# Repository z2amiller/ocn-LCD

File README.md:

# ocn-LCD

A coin-cell elapsed-time counter with a 4-digit LCD and a magnetic off switch. While a magnet
sits at the marked end, the board is switched off. Take the magnet away and it powers up and counts
elapsed time in hours and minutes, up to 99:59 (about 100 hours). Put the magnet back and it powers
down a few seconds later; the next time the magnet comes off, counting starts again from 00:00.

The renders leave out the LCD (on the back), the coin-cell holder and the reed switch, which have no
3D models.

Status: revision 0.1, not yet built. The firmware is in [firmware/](firmware/): it runs on TI's
MSP430FR4133 LaunchPad, and its driver for this board's LCD hasn't been tried on real glass yet.

## How it works

- **Counting.** An MSP430FR4131 drives the LCD directly with its built-in LCD controller and keeps
  time from a 32.768 kHz crystal. It spends almost all its time in its deepest sleep mode with the
  display still running, so it should draw 1–2 µA while counting (see the power budget below).
- **Magnet switch.** The magnet closes a normally open reed switch (SW1). That pulls the gate of a
  P-channel MOSFET (Q1) up to the cell voltage and cuts power to everything after it. With the
  magnet away, a 10 MΩ resistor pulls the gate low and the board runs. While switched off, the only
  drain on the cell is that resistor, about 0.3 µA.
- **Reset on purpose, not by accident.** 14 µF of capacitance after the switch keeps the board
  running for several seconds after the magnet arrives, so a brief knock or switch bounce does not
  reset the count. Leaving the magnet in place longer than that powers the board down and clears it.
- **Display.** The LCD is a Good Display GDC04212: 4 digits with a colon, 1/4 duty, 3 V. It mounts
  on the back of the board, so the front carries every surface-mount part.

## Power budget

Estimates at 3.0 V and 25 °C, from the TI datasheet (SLAS865) and the part specs. They will be
replaced by measurements on the board. Until then, the firmware's
[measurements on the LaunchPad](firmware/README.md#measured-on-the-launchpad) are the nearest guide:
2.2 µA asleep with its much larger LCD.

| Item | Counting (magnet away) | Off (magnet in place) | Basis |
|---|---|---|---|
| MCU asleep (LPM3.5), with the 32 kHz crystal, RTC, LCD controller and charge pump running | 0.94 µA | 0 | Datasheet typical, supervisor (SVS) off |
| LCD glass: recharging the segments about 30 times a second | 0.2–1 µA | 0 | Estimate from typical TN glass capacitance (~2 nF); the biggest unknown |
| Waking once a minute to advance the count and rewrite the display | ~0.01 µA | 0 | ~2 ms at ~0.4 mA per wake; waking every second instead would cost ~0.8 µA |
| Colon blink | ~0 | 0 | Done by the LCD hardware, no CPU wake |
| Gate pull-down R3 (10 MΩ across the cell while the reed is closed) | 0 | 0.3 µA | 3.0 V / 10 MΩ |
| Q1 MOSFET leakage while off | – | a few nA | Typical; the datasheet maximum is specified at 30 V |
| Hold-up capacitors C1–C3, leakage | ~1 nA | 0 | MLCC insulation resistance; under 0.1 µA even at the spec minimum |
| Reset pull-up, reed switch, unused pins (driven low) | 0 | 0 | No DC path |
| **Total** | **about 1.2–2 µA** | **about 0.3 µA** | |

Estimated runtime on one CR2032 (225 mAh nominal), allowing about 1 %/year for the cell's own
self-discharge:

| Mode | Estimated runtime |
|---|---|
| Counting continuously | about 11–18 years |
| Off (magnet in place) | over 40 years |

Both are longer than a CR2032's rated shelf life of about 10 years, so in practice the cell's age
sets the limit, not this circuit. Cold reduces the cell's usable capacity, so expect less in cold
conditions.

Firmware choices that keep it there:
- Leave the voltage supervisor (SVS) off in LPM3.5; it costs about 0.2 µA. The brownout reset stays
  on regardless.
- Update the count once a minute, not once a second.
- Blink the colon with the LCD hardware, not by waking the CPU.
- Drive every unused pin low, including the RX pin when nothing is connected to it.

## Placing the magnet

The reed switch is at the end marked MAGNET DISABLE and runs along the length of the board. It
responds to field along its own length, so use a magnet magnetized through its flat faces (a
neodymium cylinder or disc), at that end, with its axis along the board and its face toward the
board's end. SW1's axis is 4.4 mm in from the long edge that carries the LCD pins, and a magnet
centered on that line gives the most margin.

A magnet centered on the board's width sits about 9 mm off SW1's axis and puts roughly half to a
quarter as much field along it. Even so, a model of a typical 10 × 8 mm N42 cylinder (no nearby
steel) gives several times the switch's ~2–3 mT pull-in out to about 20 mm. Check the actual magnet
on the bench, especially if steel sits near it.

The switch lets go only once the magnet is a few centimeters away (the same model puts it at about
35–40 mm in line), so move the magnet well clear to start counting.

## Key parts

| Ref | Part | LCSC |
|---|---|---|
| U1 | TI MSP430FR4131IPM, LQFP-64 (FR4132/FR4133 also fit) | C1879660 |
| DS1 | Good Display GDC04212 4-digit LCD, 12 pins at 2.54 mm | none (hand-soldered) |
| BT1 | Lian Xin BS-CR2032-8 coin-cell holder, for a CR2032 | C7498149 |
| SW1 | Littelfuse 59170-1-S-00-D reed switch, normally open, 10–15 AT | C315909 |
| Q1 | AO3401A P-channel MOSFET, SOT-23 | C15127 |
| Y1 | TKD SF32WK32768D31T002 32.768 kHz crystal, 3215, 12.5 pF (any 3215 12.5 pF crystal fits) | C271654 |

Every part in the BOM carries its LCSC number. The LCD, J1 and TP3 are left out of the BOM and the
placement file. The passives are 0603 and 1206.

## Ordering

JLCPCB can make the board and fit all the surface-mount parts. [docs/ORDERING.md](docs/ORDERING.md)
walks through the order, screen by screen.

## Assembly

1. **Surface-mount parts first, all on the front.** A stencil helps with the 0.5 mm pitch MCU. The
   holder and the reed switch are rated for reflow, so a hotplate works.
2. **LCD last, by hand.** The LCD is through-hole on the back. Solder it after reflow and keep the
   iron off the glass. The silkscreen marks its pin 1.
3. **Programming header (J1).** It is only needed on the bench.
4. **Battery.** Fit the CR2032 after programming.

## Programming

The MCU is programmed over Spy-Bi-Wire from the eZ-FET programmer on a TI MSP-EXP430FR4133
LaunchPad. Any MSP430 LaunchPad with an eZ-FET should also work. J1 carries the four programming
signals plus the MCU's serial port.

1. **Take the coin cell out.** The LaunchPad powers the board at 3.3 V, and with a cell fitted it
   would push current back into it. The board's silkscreen says so too.
2. **Pull every jumper off the LaunchPad's J101 isolation block.** That disconnects the
   LaunchPad's own MCU, so the eZ-FET talks only to this board.
3. **Wire J1 to J101 with dupont jumpers.** Use the J101 pins on the eZ-FET (emulator) side, not the
   side that runs to the LaunchPad's own MCU:

   | ocn-LCD J1 | LaunchPad J101, eZ-FET side |
   |---|---|
   | 3V | 3V3 |
   | R | SBW RST |
   | T | SBW TST |
   | GND | GND |
   | RX (optional, serial) | RXD |
   | TX (optional, serial) | TXD |

   The serial names match straight across. J101 labels its pins from the target MCU's point of
   view, so its RXD carries data into this board's RX.

4. **Flash the firmware** with TI UniFlash or Code Composer Studio. Select the MSP430FR4131 and the
   LaunchPad's eZ-FET as the connection. Or, with msp430-gcc and DSLite installed (see
   [firmware/README.md](firmware/README.md)), run `make GLASS=gdc04212 MCU=msp430fr4131 flash` in
   `firmware/`.
5. **Unplug the LaunchPad before measuring current or fitting the cell.** The programming and
   serial lines draw current of their own.

**Measuring battery current.** R2 (1 Ω, 1206) sits in series with the cell. Lift it and connect a
current meter across its pads. TP3 is a test pad on the switched 3 V supply.

## Files

- `ocn-LCD.kicad_pro`, `.kicad_sch` and `.kicad_pcb`: the KiCad 10 project. The board is 27 × 65.4 mm,
  two layers.
- `lib/`: the board's own symbols and footprints: the MSP430FR413x, the GDC04212 and its footprint,
  the coin-cell holder and the reed switch. The project's library tables point at this folder, so the
  project opens without any other library installed.
- `firmware/`: the MCU's firmware, in C for msp430-gcc, with its own README covering how it works, how
  to build and flash it, and the current measurements.
- `GERBER-ocn-LCD.zip` and `jlcpcb/production_files/` (BOM and CPL): the JLCPCB fabrication and
  assembly files. [docs/ORDERING.md](docs/ORDERING.md) explains how to use them.

## License

The board (everything outside `firmware/`) is licensed under the **CERN Open Hardware Licence
Version 2 – Permissive** (CERN-OHL-P v2). See [LICENSE](LICENSE) and [NOTICE](NOTICE).

You may make, modify, and sell boards from these files, with no obligation to
publish your changes.

The firmware in `firmware/` is licensed under the **MIT License**; see
[firmware/LICENSE](firmware/LICENSE). It is just as permissive, in the form usual for software.

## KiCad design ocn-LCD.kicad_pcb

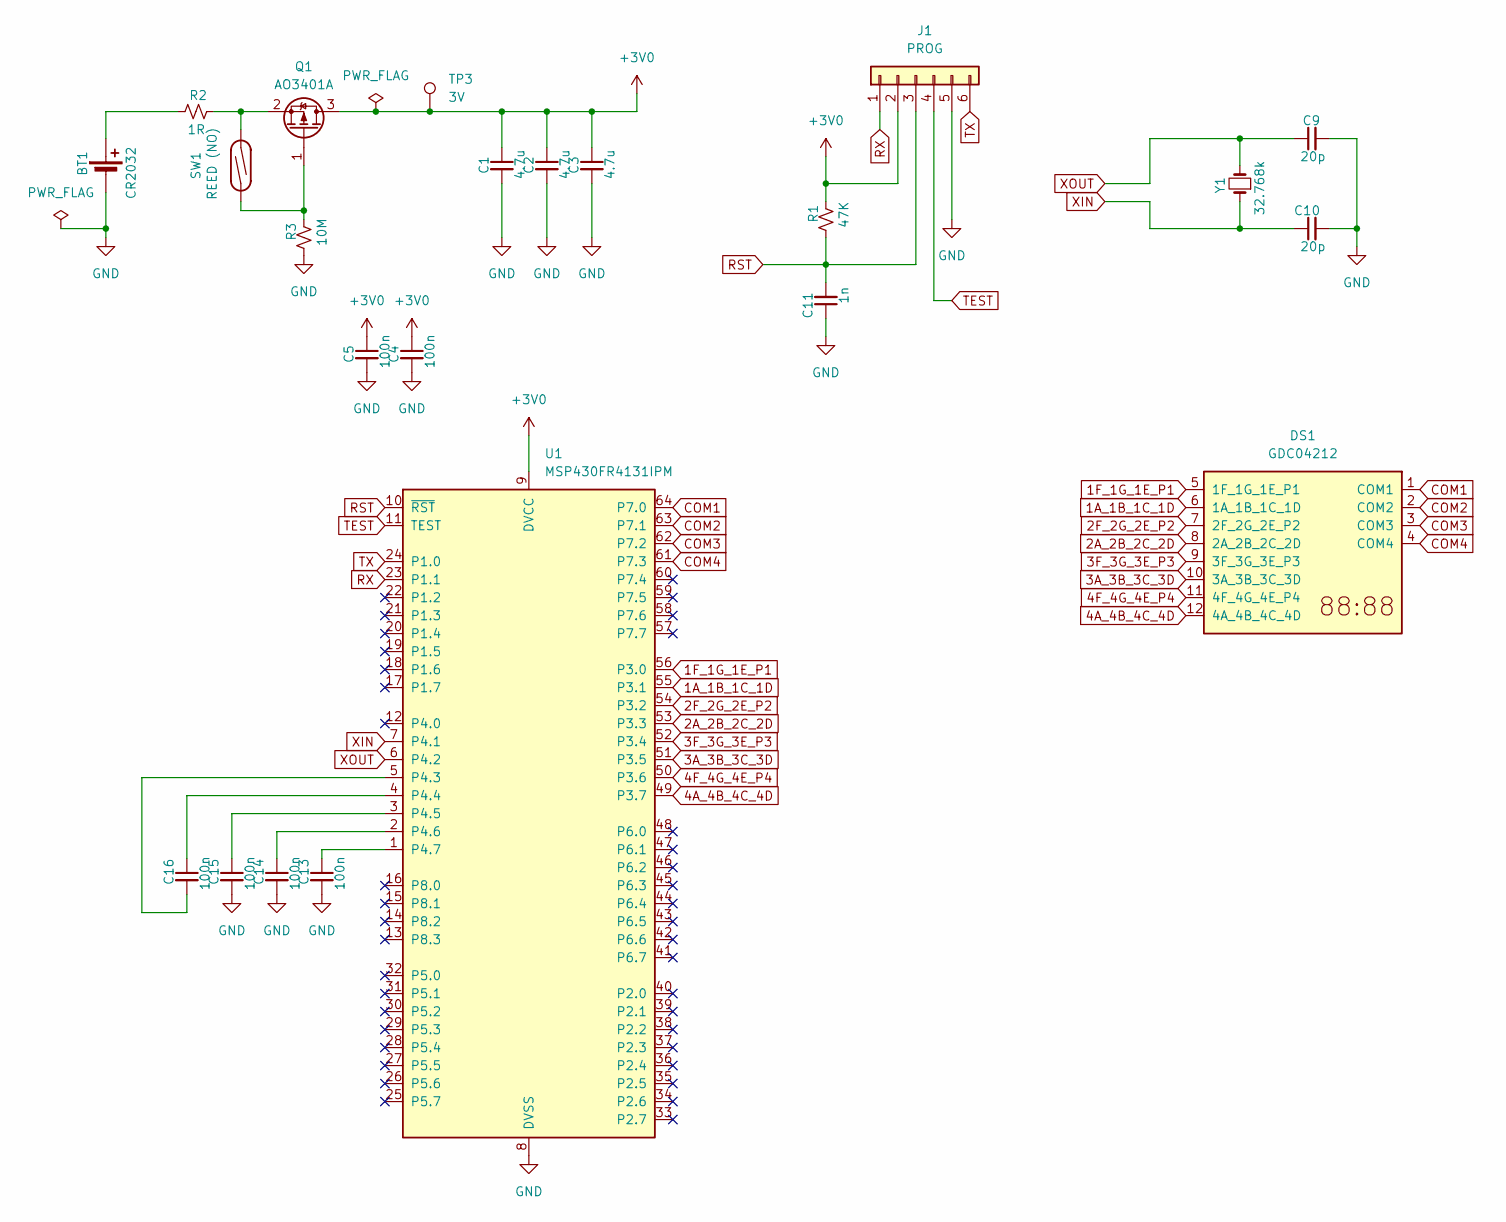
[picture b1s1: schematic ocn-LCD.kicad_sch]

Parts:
BT1: CR2032; BatteryHolder_LianXin_BS-CR2032-8_1x2032; LCSC C7498149
C1, C2, C3: 4.7u; C_1206_3216Metric; LCSC C29823
C4, C5, C13, C14, C15, C16: 100n; C_0603_1608Metric; LCSC C14663
C9, C10: 20p; C_0603_1608Metric; LCSC C1648
C11: 1n; C_0603_1608Metric; LCSC C1588
DS1: GDC04212; LCD_GDC04212_1x12_P2.54mm
J1: PROG; PinHeader_1x06_P2.54mm_Vertical
Q1: AO3401A; SOT-23; LCSC C15127
R1: 47K; R_0603_1608Metric; LCSC C25819
R2: 1R; R_1206_3216Metric; LCSC C17928
R3: 10M; R_0603_1608Metric; LCSC C7250
SW1: REED (NO); SW_SPST_REED_Littelfuse_59170_GullWing; LCSC C315909
TP3: 3V; TestPoint_Pad_1.5x1.5mm
U1: MSP430FR4131IPM; LQFP-64_10x10mm_P0.5mm; LCSC C1879660
Y1: 32.768k; Crystal_SMD_3215-2Pin_3.2x1.5mm; LCSC C271654

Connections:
1A_1B_1C_1D: DS1.6 (1A_1B_1C_1D), U1.55 (P3.1)
1F_1G_1E_P1: DS1.5 (1F_1G_1E_P1), U1.56 (P3.0)
2A_2B_2C_2D: DS1.8 (2A_2B_2C_2D), U1.53 (P3.3)
2F_2G_2E_P2: DS1.7 (2F_2G_2E_P2), U1.54 (P3.2)
3A_3B_3C_3D: DS1.10 (3A_3B_3C_3D), U1.51 (P3.5)
3F_3G_3E_P3: DS1.9 (3F_3G_3E_P3), U1.52 (P3.4)
4A_4B_4C_4D: DS1.12 (4A_4B_4C_4D), U1.49 (P3.7)
4F_4G_4E_P4: DS1.11 (4F_4G_4E_P4), U1.50 (P3.6)
+3V0: C1.1, C2.1, C3.1, C4.1, C5.1, J1.2, Q1.3 (D), R1.1, TP3.1 (1_1), U1.9 (DVCC)
COM1: DS1.1 (COM1), U1.64 (P7.0)
COM2: DS1.2 (COM2), U1.63 (P7.1)
COM3: DS1.3 (COM3), U1.62 (P7.2)
COM4: DS1.4 (COM4), U1.61 (P7.3)
GND: BT1.2 (-), C1.2, C2.2, C3.2, C4.2, C5.2, C9.2, C10.2, C11.1, C13.2, C14.2, C15.2, J1.5, R3.2, U1.8 (DVSS)
unnamed: BT1.1 (+), R2.2
unnamed: Q1.1 (G), R3.1, SW1.1
unnamed: Q1.2 (S), R2.1, SW1.2
unnamed: C16.2, U1.5 (P4.3)
unnamed: C16.1, U1.4 (P4.4)
unnamed: C15.1, U1.3 (P4.5)
unnamed: C14.1, U1.2 (P4.6)
unnamed: C13.1, U1.1 (P4.7)
RST: C11.2, J1.3, R1.2, U1.10 (~RST)
RX: J1.1, U1.23 (P1.1)
TEST: J1.4, U1.11 (TEST)
TX: J1.6, U1.24 (P1.0)
XIN: C10.1, U1.7 (P4.1), Y1.1
XOUT: C9.1, U1.6 (P4.2), Y1.2

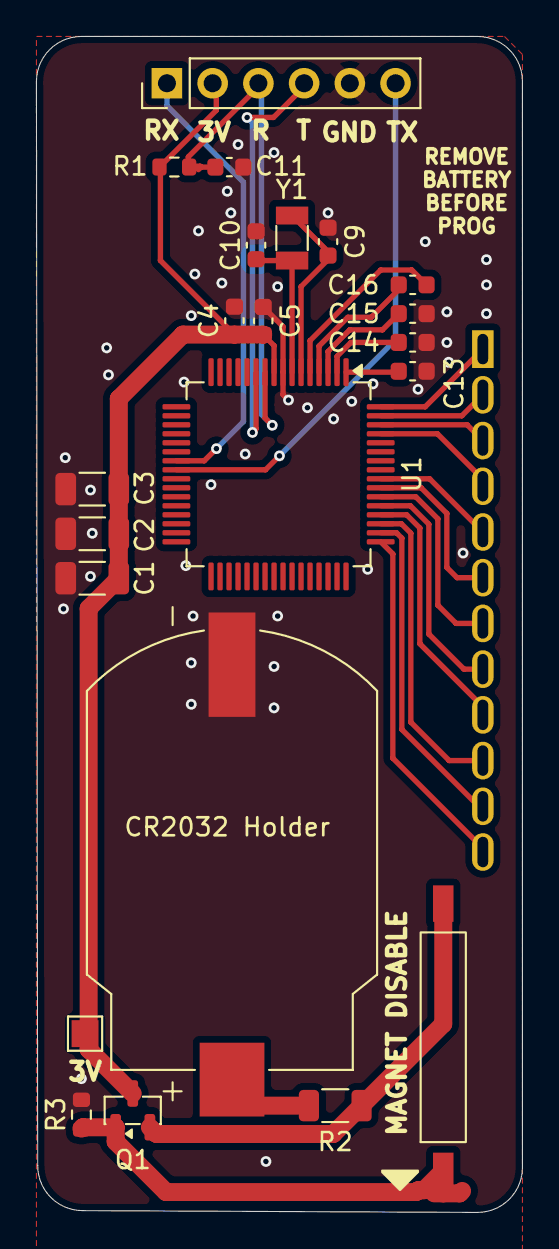
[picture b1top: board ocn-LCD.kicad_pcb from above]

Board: 2 copper layers, 27.0 x 65.3 mm, 23 parts (1 on the bottom side), 28 nets.

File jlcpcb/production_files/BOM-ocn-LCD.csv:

Comment,Designator,Footprint,LCSC,Quantity
100n,"C13,C14,C15,C16,C4,C5",C_0603_1608Metric,C14663,6
10M,R3,R_0603_1608Metric,C7250,1
1R,R2,R_1206_3216Metric,C17928,1
1n,C11,C_0603_1608Metric,C1588,1
20p,"C10,C9",C_0603_1608Metric,C1648,2
32.768k,Y1,Crystal_SMD_3215-2Pin_3.2x1.5mm,C271654,1
4.7u,"C1,C2,C3",C_1206_3216Metric,C29823,3
47K,R1,R_0603_1608Metric,C25819,1
AO3401A,Q1,SOT-23,C15127,1
CR2032,BT1,BatteryHolder_LianXin_BS-CR2032-8_1x2032,C7498149,1
GDC04212,DS1,LCD_GDC04212_1x12_P2.54mm,C9900333183,1
MSP430FR4131IPM,U1,LQFP-64_10x10mm_P0.5mm,C1879660,1
REED (NO),SW1,SW_SPST_REED_Littelfuse_59170_GullWing,C315909,1

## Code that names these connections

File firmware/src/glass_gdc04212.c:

// SPDX-License-Identifier: MIT
// The board's glass: Good Display GDC04212, 4 digits with a colon, 1/4 duty, 1/3 bias, 3.0 V. Derived from the
// spec sheet's pin table (as encoded in the GDC04212 symbol in ../lib/LowPower.kicad_sym) and the board's
// netlist; not yet checked on real glass.
//
// Glass pins 1-4 are COM1-COM4, wired to P7.0-P7.3 = L0-L3 (MCU COM0-COM3), as on the LaunchPad. The segment
// pins are wired in order to P3.0-P3.7 = L8-L15:
//
//   glass pin   MCU pin   segment on COM1  COM2  COM3  COM4
//       5        L8              1F        1G    1E    P1
//       6        L9              1A        1B    1C    1D
//       7        L10             2F        2G    2E    P2 (colon)
//       8        L11             2A        2B    2C    2D
//       9        L12             3F        3G    3E    P3
//      10        L13             3A        3B    3C    3D
//      11        L14             4F        4G    4E    P4
//      12        L15             4A        4B    4C    4D
//
// Each LCDMEM byte covers two pins: the even pin's COM3..COM0 in bits 3..0, the odd pin's in bits 7..4. So digit n
// is LCDMEM[3 + n], and every digit's byte has the same layout. P1, P3 and P4 are decimal points.
#include <msp430.h>
#include "glass.h"

// TI's header declares LCDMEM and LCDBMEM as pointers to a one-byte register, so indexing past 0 trips
// -Warray-bounds even though the memory is there.
#pragma GCC diagnostic ignored "-Warray-bounds"

#define SEG_F 0x01                               // even pin, COM1
#define SEG_G 0x02                               // even pin, COM2
#define SEG_E 0x04                               // even pin, COM3
#define SEG_P 0x08                               // even pin, COM4: decimal point, or the colon on digit 2
#define SEG_A 0x10                               // odd pin, COM1
#define SEG_B 0x20                               // odd pin, COM2
#define SEG_C 0x40                               // odd pin, COM3
#define SEG_D 0x80                               // odd pin, COM4

static const uint8_t digit[10] = {
    SEG_A | SEG_B | SEG_C | SEG_D | SEG_E | SEG_F,             // 0
    SEG_B | SEG_C,                                             // 1
    SEG_A | SEG_B | SEG_D | SEG_E | SEG_G,                     // 2
    SEG_A | SEG_B | SEG_C | SEG_D | SEG_G,                     // 3
    SEG_B | SEG_C | SEG_F | SEG_G,                             // 4
    SEG_A | SEG_C | SEG_D | SEG_F | SEG_G,                     // 5
    SEG_A | SEG_C | SEG_D | SEG_E | SEG_F | SEG_G,             // 6
    SEG_A | SEG_B | SEG_C,                                     // 7
    SEG_A | SEG_B | SEG_C | SEG_D | SEG_E | SEG_F | SEG_G,     // 8
    SEG_A | SEG_B | SEG_C | SEG_D | SEG_F | SEG_G,             // 9
};

#define DIGIT_BYTE(n) (3 + (n))                  // n = 1..4
#define COLON_BYTE    DIGIT_BYTE(2)
#define COLON_BIT     SEG_P

void glass_pins(void)
{
    SYSCFG2 |= LCDPCTL;                          // R13, R23, R33, LCDCAP0 and LCDCAP1 to the LCD
    LCDPCTL0 = 0xFF0F;                           // L0-L3 (COMs) and L8-L15 (segments); nothing else
    LCDPCTL1 = 0;
    LCDPCTL2 = 0;
}

void glass_init(void)
{
    // Same timing and bias as the LaunchPad glass (see glass_launchpad.c): 32 Hz frames, the low-power waveform
    // and the switched bias reference. VLCD_6 is 2.96 V for the glass's 3.0 V; check the contrast on real glass,
    // and raise the frame rate (LCDDIV_3, 64 Hz) if it flickers.
    LCDCTL0 = LCDDIV_7 | LCDSSEL_0 | LCD4MUX | LCDLP;
    LCDVCTL = LCDCPEN | LCDREFEN | LCDREFMODE | VLCD_6 | LCDCPFSEL0 | LCDCPFSEL1 | LCDCPFSEL2 | LCDCPFSEL3;
    LCDMEMCTL |= LCDCLRM | LCDCLRBM;             // clears the COM assignments too, so set them after
    LCDCSSEL0 = 0x000F;                          // L0-L3 are COMs
    LCDCSSEL1 = 0;
    LCDCSSEL2 = 0;
    LCDM0 = 0x21;                                // L0 = COM0, L1 = COM1
    LCDM1 = 0x84;                                // L2 = COM2, L3 = COM3
    LCDBMEM[COLON_BYTE] = COLON_BIT;             // only the colon blinks, at 1 Hz
    LCDBLKCTL = LCDBLKPRE_4;
    LCDBLKCTL |= LCDBLKMOD_1;
    LCDCTL0 |= LCDON;
}

void glass_show(const uint8_t digits[4])
{
    for (uint8_t i = 0; i < 4; i++) {
        LCDMEM[DIGIT_BYTE(i + 1)] = digit[digits[i]];
    }
    LCDMEM[COLON_BYTE] |= COLON_BIT;
}
